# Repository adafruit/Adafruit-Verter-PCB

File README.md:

## Adafruit Verter Buck/Boost Breakout PCB
<a href="http://www.adafruit.com/products/2190"><br/>
Click here to purchase one from the Adafruit shop</a>

Convert just about any battery pack to 5V with VERTER - our fresh new Buck-Boost power converter. VERTER can take battery voltages from 3-12VDC and output a nice 5V DC, which makes it a perfect universal power supply for your portable project! Where Verter really shines is when you have a battery or power range that can fluctuate a lot, or you don't know what you'll end up using.

It operates smoothly over the 3-12V range, moving from a boost converter (3-5V in) to a buck converter (5-12V in) on the fly. Please note! This chip can do both, but it really works better as a buck converter than a boost. If you need a full 500mA out, it will struggle as it gets down to 3V and the output will sag to about 4.8V (which is still within standard USB power specs). If you only need something to boost a voltage up to 5V and you want it to be really good at it, check out our PowerBoost series, which excel at that.

Like our popular 5V 1A USB wall adapter, we tweaked the output to be 5.2V instead of a straight-up 5.0V so that there's a little bit of 'headroom' long cables, high draw, the addition of a diode on the output if you wish, etc. The 5.2V is safe for all 5V-powered electronics like Arduino, Raspberry Pi, or Beagle Bone while preventing icky brown-outs during high current draw because of USB cable resistance.

PCB files for the Verter Buck/Boost Breakout
- https://www.adafruit.com/products/2190

### License

Adafruit invests time and resources providing this open source design, please support Adafruit and open-source hardware by purchasing products from [Adafruit](https://www.adafruit.com)!

All text above must be included in any redistribution

Designed by Limor Fried/Ladyada for Adafruit Industries.
Creative Commons Attribution/Share-Alike, all text above must be included in any redistribution. 
See license.txt for additional information.

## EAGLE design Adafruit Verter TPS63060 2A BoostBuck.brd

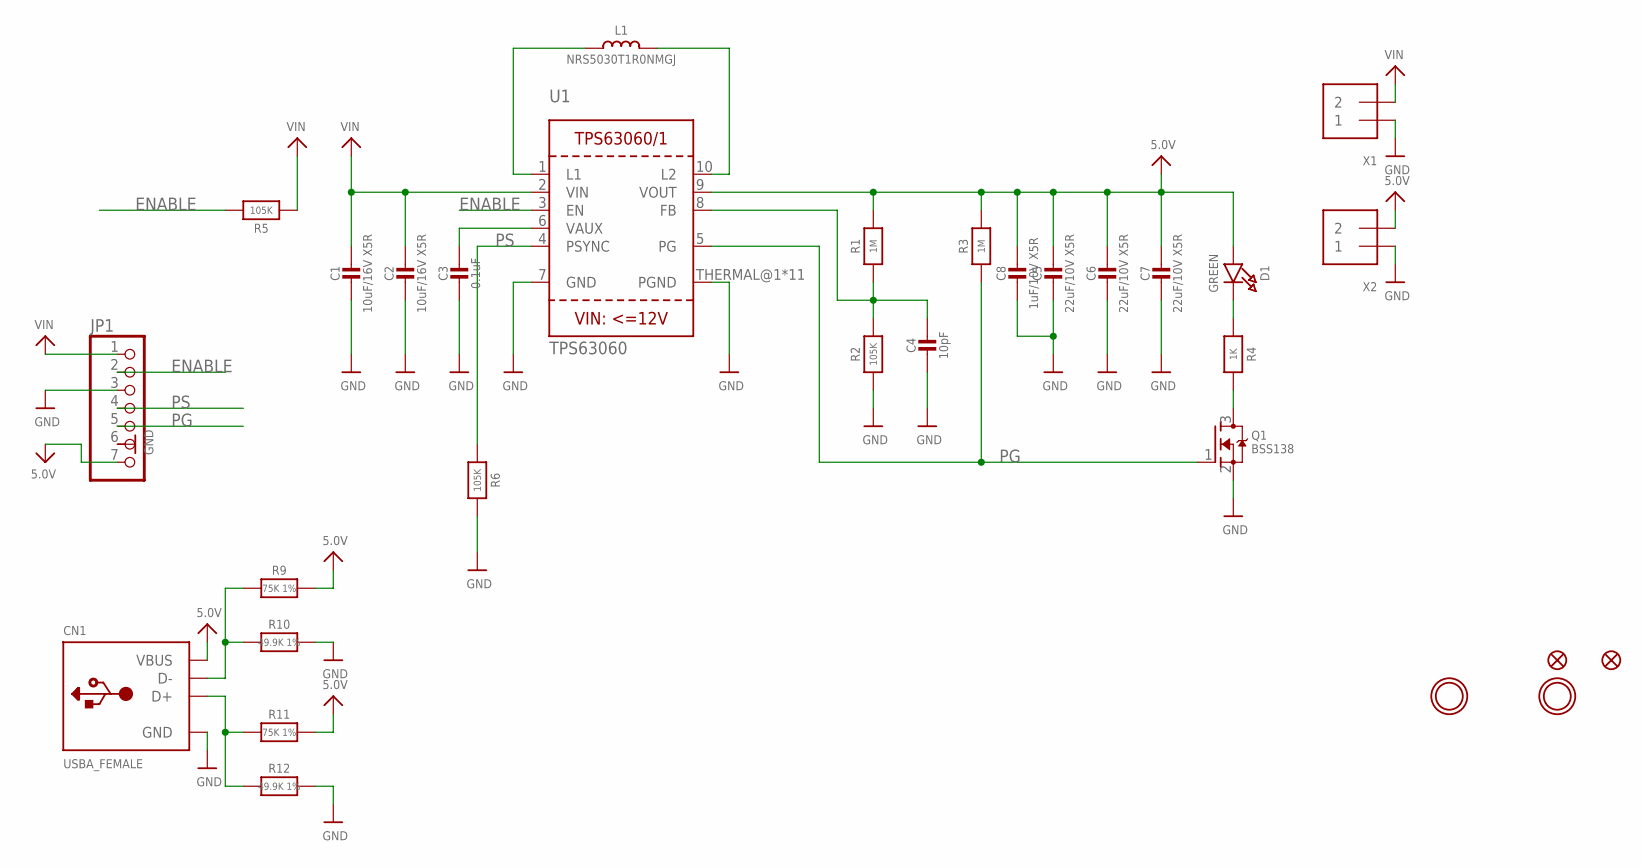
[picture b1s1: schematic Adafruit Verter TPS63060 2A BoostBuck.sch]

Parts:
C1, C2: 10uF/16V X5R; 0805-NO
C3: 0.1uF; 0805-NO
C4: 10pF; 0805-NO
C5, C6, C7: 22uF/10V X5R; 0805-NO
C8: 1uF/10V X5R; 0805-NO
CN1: USBA_FEMALE; USB_HOST-PTH
D1: GREEN; CHIPLED_0805_NOOUTLINE
FID1, FID2: FIDUCIAL""; FIDUCIAL_1MM
JP1: HEADER-1X770MIL; 1X07_ROUND_70
L1: NRS5030T1R0NMGJ; INDUCTOR_5X5MM_TDK_VLC5045
Q1: BSS138; SOT23-WIDE
R1, R3: 1M; 0805-NO
R2, R5, R6: 105K; 0805-NO
R4: 1K; 0805-NO
R9, R11: 75K 1%; 0805-NO
R10, R12: 49.9K 1%; 0805-NO
U1: TPS63060; PWSON-N10
U$15, U$17: MOUNTINGHOLE2.5; MOUNTINGHOLE_2.5_PLATED
X1, X2: TERMBLOCK_1X2; TERMBLOCK_1X2-3.5MM

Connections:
5.0V: C5.1, C6.1, C7.1, C8.1, CN1.VBUS, D1.A, JP1.7, R1.2, R3.2, R9.2, R11.2, U1.9 (VOUT), X2.2
D+: CN1.D+, R11.1, R12.1
D-: CN1.D-, R9.1, R10.1
ENABLE: JP1.2, R5.2, U1.3 (EN)
GND: C1.2, C2.2, C3.2, C4.2, C5.2, C6.2, C7.2, C8.2, CN1.GND, JP1.3, JP1.6, Q1.2 (S), R2.1, R6.2, R10.2, R12.2, U1.7 (GND), U1.THERMAL@1 (PGND), U1.THERMAL@5 (PGND), U1.THERMAL@6 (PGND), U1.THERMAL@7 (PGND), U1.THERMAL@8 (PGND), U1.THERMAL@9 (PGND), U1.THERMAL@10 (PGND), U1.THERMAL@11 (PGND), U1.THERMAL@12 (PGND), U1.THERMAL@13 (PGND), U1.THERMAL@14 (PGND), X1.1, X2.1
unnamed: L1.P$1 (1), U1.1 (L1)
unnamed: L1.P$2 (2), U1.10 (L2)
unnamed: C3.1, U1.6 (VAUX)
unnamed: D1.C, R4.1
unnamed: C4.1, R1.1, R2.2, U1.8 (FB)
unnamed: Q1.3 (D), R4.2
PG: JP1.5, Q1.1 (G), R3.1, U1.5 (PG)
PS: JP1.4, R6.1, U1.4 (PSYNC)
VIN: C1.1, C2.1, JP1.1, R5.1, U1.2 (VIN), X1.2

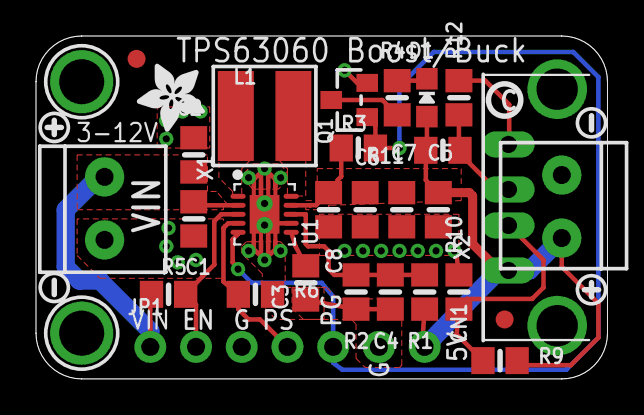
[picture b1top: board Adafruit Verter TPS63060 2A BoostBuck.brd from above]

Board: 2 copper layers, 31.8 x 19.1 mm, 37 parts (1 on the bottom side), 14 nets.

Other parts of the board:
U$22, U$23: SYMBOL_PLUS
U$24, U$25: SYMBOL_MINUS
U$27: ADAFRUIT_3.5MM
U$37: VERTERLOGO
U$38: PCBFEAT-REV-040

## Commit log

2015-10-15 init
2015-10-15 add url n stuff

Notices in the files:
parts and their libraries:
microbuilder: This work is placed in the public domain, and may be freely used for commercial and non-commercial work with the following conditions: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
